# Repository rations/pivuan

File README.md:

<p align="center"><b>Devuan with sysvinit for the Raspberry Pi.</b></p>

---

Pivuan is a minimal [Devuan](https://www.devuan.org/) 6 "excalibur" image for the Raspberry Pi,
built with the [Armbian](https://www.armbian.com/) build framework. It boots with **sysvinit**
instead of systemd, feels like an Armbian minimal image (fast boot, first-boot setup wizard,
configuration tool), and gets its updates from Devuan and from its own apt repository.

- **Minimal**: a small console system (about 850 MB used) with networking, SSH and the
  `pivuan-config` tool. Add only what you need.
- **sysvinit, no systemd**: `init` is PID 1, with elogind, eudev and ifupdown. Packages that
  would pull in systemd are left out.
- **Desktop in one command**: XFCE or MATE with a LightDM login screen, installed from the
  Devuan archive (with XLibre from the Pivuan apt repository) by `pivuan-config`, SonicDE
  (from KDE Plasma, built by Pivuan), or
  **Pivuan Audio** for music production (JWM and JACK), which also runs Windows plugins.
- **Kept up to date**: Devuan's security updates through apt, and the Raspberry Pi kernel,
  firmware, board support and `pivuan-config` through the Pivuan apt repository.

Pivuan is built for the **Raspberry Pi 5** and uses the Raspberry Pi Foundation's kernel. The
same image is built for the other 64-bit boards it supports (Raspberry Pi 3 and 4), which are
less tested.

## Download

Get the latest image from **[Releases](https://github.com/rations/pivuan/releases)**: the
`Pivuan_<version>_Rpi4b_excalibur_current_<kernel>_minimal.img.xz` file and its `.sha` file.

Check the download (optional):

```sh
sha256sum -c Pivuan_*.img.xz.sha
```

## Install

Write the image to a microSD card (8 GB or larger). Any of these works:

- **balenaEtcher**: pick the `.img.xz` file and the card, then Flash.
- **Raspberry Pi Imager**: *Choose OS* → *Use custom* → the `.img.xz` file. Don't use its
  "OS customisation" settings; Pivuan's first-boot wizard does that.
- **Linux command line** (replace `/dev/sdX` with your card; check with `lsblk`, this erases it):

  ```sh
  xzcat Pivuan_*.img.xz | sudo dd of=/dev/sdX bs=4M conv=fsync status=progress
  ```

The image is `xz`-compressed, not a tar archive: use `xzcat`, `unxz` or `xz -d`, not `tar`.

## First boot

1. Put the card in the Pi, connect a screen and keyboard (or Ethernet), and power on.
2. The filesystem grows to fill the card and the **Pivuan setup wizard** starts on the screen.
   It asks for:
   - a new **root password**,
   - your **user name and password** (this user can use `sudo`, and always with a password;
     there is no automatic login),
   - Wi-Fi, if no network cable is plugged in.

   It also sets your time zone and language.
3. You end up at a shell with a welcome screen showing the system's state and tips.

Without a screen, connect Ethernet, find the Pi's address on your router and log in with
`ssh root@<address>` using the password **`1234`**; the same wizard then starts and makes you
change it.

## Boot splash

While Pivuan starts, the screen shows the Pivuan logo: a band of light sweeps it in, then
electricity runs along its circuit traces until the login appears. It also shows at shutdown
and restart. This is plymouth with the Pivuan theme (`pivuan-plymouth-theme`), which is on the
image and is installed with each desktop.

- Press **Esc** during the boot to see the boot messages instead.
- To turn the splash off, add `nosplash` to the line in `/boot/firmware/cmdline.txt` and
  restart. Remove it again to bring the splash back.

## Desktop

The image is minimal on purpose. To add a desktop, log in and install **Pivuan Audio**,
the desktop Pivuan is made for, or XFCE, MATE or SonicDE.

One desktop is installed at a time. To change to another one, remove the desktop first, from
the text login and not from a terminal in the desktop: removing it closes the desktop, and the
removal with it. Press **Ctrl+Alt+F1** for the text login (Pivuan Audio has its login screen on
tty1, so use **Ctrl+Alt+F2** there), log in and run the remove command of your desktop
(`AUDI02`, `XFCE02`, `MATE02` or `SONI02` in place of `01`).

### Pivuan Audio

A desktop for audio production on the Raspberry Pi 5, with JACK and PulseAudio and without
PipeWire:

```sh
sudo pivuan-config --cmd AUDI01    # Pivuan Audio
```

It installs:

- **JWM** on the **XLibre** X server, built for Devuan excalibur (no backports) and installed
  from the Pivuan apt repository, with the **picom** compositor for smooth window moves,
- the **xlogin** login screen on tty1 instead of a display manager (it appears as soon as the
  install finishes; tty2 to tty6 keep their text login),
- **JACK** with realtime scheduling for the `audio` group, and the Pivuan audio applications
  from the Pivuan apt repository: Jack Graph, JackDAW, NAMp, NAMix, lvtuner, DRUMix and
  CPU Power, and **TONE3000** (its amp and effects plug-in as VST3 and LV2, and the standalone
  program, for every user; tones download from tone3000.com),
- **vstbridge** for 64-bit and 32-bit Windows VST2, VST3 and CLAP plugins in the audio
  programs ("vstbridgectl" in the Audio menu), with **Wine** and **FEX** for Windows programs,
  such as plugin installers and license managers: they open from a right-click in pcmanfm
  ("Wine Windows Program Loader"). Installed Windows programs are in the **Wine** menu, which
  updates itself, with Wine Configuration and Uninstall Windows Programs, and the shortcuts
  installers put on the desktop show as desktop icons. Plugins protected by iLok (PACE),
  such as Neural DSP's, run with a license activated to the computer in iLok License Manager
  (USB iLok keys don't work in Wine). They, and iLok License Manager, need iLok's service
  running before they open: open **Plugin Licenses** in the Audio menu, wait for "Ready" (about
  half a minute), then open your DAW or iLok License Manager. Once the plugins have loaded you
  can close the window; the service (about 1 GB of memory) stops by itself when you close the
  DAW. A plugin that loads without it says it has
  no license; if JackDAW then skipped it, Options > Plugins… > Scan tries it again.
  Everything uses the Wine prefix `~/.wine`. How this works without DXVK:
  [wine-fex-info.md](wine-fex-info.md),
- **PulseAudio** for everything else: HDMI, Bluetooth speakers and headphones, the browser and
  media player. The speaker in the tray opens a volume slider with Mute and a button for
  Volume Control (pavucontrol); a right click opens Volume Control, and its scroll wheel
  changes the volume. A USB audio interface is an output as soon as it is plugged in (if
  PulseAudio leaves it at the profile Off, it is given its best output profile; if it could
  not open the interface, it is switched off and on again). While JACK
  runs, PulseAudio lets it have the sound card and plays into JACK instead ("JACK (audio
  interface)" in Volume Control); when JACK stops, it takes the card back,
- lxterminal, pcmanfm, mousepad, Celluloid, lxrandr and lxappearance, with the Pivuan icons
  (drawn for the Haiku operating system). In pcmanfm and on the desktop, a right click on a
  zip or tar archive (.zip, .tar, .tar.gz, .tar.xz, .tar.bz2, .tar.zst) has **Extract Here**:
  it unpacks next to the archive, into a folder named after it when it holds several files,
  and never overwrites anything.
  **Extra monitors**: Settings > Monitor Settings (lxrandr, "Display Settings") sets each
  monitor's resolution and where it is. The first monitor in its list stays put (its Position
  is greyed out); each other one is placed on its left or right ("On left", "On right"), above
  or below it, or shows the same picture: that is "Default" (best when both have the same
  resolution). After Apply, confirm within 15 seconds, or the old layout comes back. Save
  keeps it: the saved layout is applied at each login, as are other programs in
  `~/.config/autostart` meant for LXDE or any desktop. Every monitor gets its own desktop with
  the background, and with a touchscreen, touch stays on the touchscreen's own monitor (a
  Raspberry Pi touch display, or else the smallest monitor),
- the folders Desktop, Downloads, Documents, Music, Videos, NAM, Impulse Responses, `.vst3`
  and `.lv2` in each home, bookmarked in pcmanfm (the files in Desktop show on the desktop),
- **NetworkManager** and **blueman** in the tray, and **Brave Origin**,
- **Desktop Settings** (Settings in the menu), in four tabs that fit small screens:
  **Background** (the Pivuan backgrounds, black by default, or any picture, and icons on the
  desktop, on by default), **Screen** (the **brightness**, turning the screen off after 10
  minutes without use, off by default, and long press on a touchscreen), **Panel** (its size,
  color, by default the grey of the Pivuan logo, hiding it until the mouse reaches the bottom
  edge, and the on-screen keyboard) and **Panel Icons** (program icons on the panel, all drawn
  at the same size). **Apply** lights up when there is a change to apply. It saves to
  `~/.config/pivuan/desktop.conf`. Brightness uses the screen's backlight, or the monitor's
  own setting over HDMI (DDC/CI), or else dims the picture; the sun button on the panel opens
  just the brightness slider.

**Screenshots**: Print saves the whole screen, Alt+Print an area you drag out, and
Super+Print a window you click, as PNG files in `~/Pictures`. **Accessories > Screenshot** in
the menu takes the same three, after a delay if you like, then lets you name the picture and
choose its folder (`~/Pictures` at first).

The **Pivuan menu** (jgmenu) is on the Pivuan button in the tray, on a right click on the
desktop, and on Alt+F1. It has Terminal, Home and Web Browser, then the programs by category
(Accessories, Audio, Video, Internet, Settings, System and so on, from the programs' own menu
entries, so a program you install shows up in its category by itself), the Windows programs
installed in Wine, and Log Out, Reboot and Shut Down, which ask first. Its look is in
`/etc/pivuan/jgmenurc`; settings in `~/.config/jgmenu/jgmenurc` override it. Each user's
`~/.jwmrc` includes `/etc/jwm/pivuan.jwmrc`; add your own settings to
`~/.jwmrc`. `sudo pivuan-config --cmd AUDI02` removes it and brings back the text login.

#### Touchscreens

Pivuan Audio works on a touchscreen with no keyboard attached. When a touchscreen is
connected:

- The **login screen** shows an on-screen keyboard under the login box, in the keyboard
  layout chosen at first boot. **Keyboard** on the login screen, or **Hide** on the
  keyboard, puts it away and brings it back. Options → On-screen keyboard sets it to
  Automatic, Always or Never. With **Log in automatically** ticked, the machine starts
  without asking for a password at all.
- The **desktop** has a keyboard button on the panel that shows and hides **Onboard**, the
  on-screen keyboard, docked above the panel. It is also Settings → On-screen Keyboard in the
  menu. In Desktop Settings, set it to Automatic (only with a touchscreen), Always or Never.
- **Long press for right click:** hold a finger still for a moment and lift it, for the
  menus a right click opens (JackDAW's track and record menus, disconnecting in jack-graph,
  pcmanfm and the desktop). A tap is a click, and a moving finger drags: dials, selections,
  and window borders and corners to resize them. Pinch to zoom in the web browser is off
  while it runs; Desktop Settings → Screen turns it off.
- **Two fingers scroll:** move two fingers up and down (or sideways) and the page or list
  under them follows, wherever the mouse wheel scrolls (it turns the wheel).
- **Onboard comes up by itself** when you tap a text box in GTK and Qt programs and in the
  web browser, and goes away afterwards; the panel button is for the rest. It stays down
  while a USB or Bluetooth keyboard is plugged in.
- The panel is 48 pixels and its icons 32, window borders and title bars are bigger, and
  tooltips are off (a tap would leave them standing). Desktop Settings changes the panel.
- In GTK 3 programs (JackDAW, Desktop Settings, pcmanfm) a tap is a mouse click, so their
  drop-down lists stay open and dragging works; scroll their lists with two fingers or
  the scroll bars.
- If the screen is powered from the Pi's USB, an audio interface on the same USB can be too
  much for it: the Pi 5 gives USB 600 mA in all unless its supply is the 5 A one. Power the
  screen separately, or plug the interface in before starting.

A touchscreen is an input device the kernel marks as *direct*
(`/sys/class/input/input*/properties`). A touchpad or a mouse does not count.

### XFCE and MATE

General-purpose desktops:

```sh
sudo pivuan-config --cmd XFCE01    # XFCE
sudo pivuan-config --cmd MATE01    # MATE
```

This installs, from the Devuan archive:

- **XFCE** with `xfce4-terminal` and the Pivuan menu icon, or **MATE** with `mate-terminal`,
  both with the black Pivuan background,
- the **XLibre** X server from the Pivuan apt repository (as on Pivuan Audio), with the
  **picom** compositor for smooth window moves,
- the **LightDM** login screen (no automatic login),
- **NetworkManager** with its tray applet (your wired and Wi-Fi settings are moved over),
- **PulseAudio** for sound and Bluetooth audio,
- the **Pivuan icon theme** (the icons of the Haiku operating system), to pick in Appearance;
  the desktops keep the Numix icons,
- **Brave Origin** as the web browser, from [Brave's apt repository](https://brave.com/linux/).

When it finishes, the login screen appears. Log in with the user you created in the wizard.

### SonicDE

[SonicDE](https://github.com/Sonic-DE) is a desktop forked from KDE Plasma 6 that keeps to X11:

```sh
sudo pivuan-config --cmd SONI01    # SonicDE (about 1.5 GB)
```

SonicDE needs a newer Qt and KDE Frameworks than Devuan has, so Pivuan builds the whole desktop,
with its own Qt and frameworks, into `/opt/sonicde` and publishes it in an apt repository of its
own, the [Pivuan SonicDE apt repository](https://github.com/rations/pivuan-sonicde), which
`pivuan-config` adds (signed with the same key as the Pivuan apt repository). Devuan's own Qt
programs are left as they are. This installs:

- **SonicDE**: the desktop and panel, the sonic-win window manager (it draws its own effects,
  without picom), System Settings, the file manager, terminal, system monitor, screenshot tool
  and disk tool, with the **Silver Dark** look, the panel along the bottom and the
  SonicBallLightning background (the lock screen keeps the black Pivuan one),
- programs from Devuan that SonicDE has none of: **FeatherPad** (text editor), **VLC** (video
  and music), **LXQt Archiver**, **qpdfview** (PDF viewer), **LXImage** (image viewer) and
  **Qalculate** (calculator),
- the **XLibre** X server from the Pivuan apt repository, as on the other desktops,
- the **LightDM** login screen (no automatic login),
- **NetworkManager**, **PulseAudio** and **Bluetooth**, in the panel (your wired and Wi-Fi
  settings are moved over),
- **Onboard**, the on-screen keyboard, which comes up when a text box is tapped on a
  touchscreen,
- **Brave Origin** as the web browser, from [Brave's apt repository](https://brave.com/linux/).

When it finishes, the login screen appears. Log in with the user you created in the wizard.
`sudo pivuan-config --cmd SONI02` removes it, and the Pivuan SonicDE apt repository with it.

## pivuan-config

`pivuan-config` is the configuration tool: Armbian's `armbian-config` adapted for sysvinit.
Run it with a menu, or give it a command:

```sh
sudo pivuan-config                 # menu: system, network, localisation, software, desktops
sudo pivuan-config --cmd help      # list the commands
pivuan-config --help
pivuan-config --doc                # this README
```

Network settings: with a desktop installed, NetworkManager runs the network. Use the
network icon in the panel, or **Network → Network connections** in `pivuan-config` (the
same as `sudo nmtui`). On a console-only system, **Network → Switch to NetworkManager**
moves your wired and Wi-Fi settings over to it first.

## Updates

```sh
sudo apt update && sudo apt full-upgrade
```

- Everything from Devuan (the base system, the desktop, security fixes) comes from
  `deb.devuan.org`.
- The kernel, device trees, board support and `pivuan-config` come from the **Pivuan apt
  repository**, `https://rations.github.io/pivuan`, which Pivuan images already use. So do
  Pivuan Audio's XLibre, audio applications, vstbridge and Wine. The repository is
  signed with the key `34EA 4F11 5D83 793B 6C80  3155 4769 929F 204B 18CD`.

The kernel follows the Foundation's `rpi-6.18.y` long-term branch. Each week the build checks
for a new kernel point release (they carry the security fixes); when there is one, a new
image is released here and the kernel packages reach installed systems through `apt`.

## How Pivuan is made

Pivuan is a fork of the Armbian build framework that builds Devuan with sysvinit:

| Repository | What it is |
|---|---|
| [rations/build](https://github.com/rations/build) (branch `pivuan`) | Armbian build framework fork: Devuan excalibur support, sysvinit init scripts for Armbian's first-boot and board services, the image and apt-repository workflows |
| [rations/configng](https://github.com/rations/configng) | `armbian-config` (configng) fork, packaged as `pivuan-config`: a sysvinit service backend and the Devuan desktop install |
| [raspberrypi/linux](https://github.com/raspberrypi/linux) | The Raspberry Pi Foundation's kernel, pinned to a tested `rpi-6.18.y` commit |
| [rations/pivuan](https://github.com/rations/pivuan) (this repository) | Project page, releases (images), the apt repository (`gh-pages` branch), and the XLibre, vstbridge, Pivuan icon theme, boot splash, Desktop Settings and long press package builds |
| [rations/vstbridge](https://github.com/rations/vstbridge) (branch `arm64`) | vstbridge, the Windows plugin bridge, and the build of its Wine with FEX ([wine-fex-info.md](wine-fex-info.md)) |

Images are built by GitHub Actions in `rations/build`, from Devuan packages checked against
Devuan's signing keys. The packages in the image, in each desktop and in the Pivuan apt
repository are listed in [packages/](packages/).

## Thanks

Pivuan exists because of the work of two projects:

- **[Armbian](https://www.armbian.com/)**: the build framework, board support, first-boot
  wizard, `armbian-config` and the kernel packaging are theirs. Pivuan is their work, adapted
  to boot without systemd. Please support them: <https://www.armbian.com/donate/>
- **[Devuan](https://www.devuan.org/)**: the whole operating system, init freedom, and years
  of keeping Debian usable without systemd. Please support them: <https://www.devuan.org/os/donate>

Also thanks to the [Raspberry Pi Foundation](https://www.raspberrypi.com/) for the kernel and
firmware, to [Debian](https://www.debian.org/), which Devuan is based on, and to the
[Haiku](https://www.haiku-os.org/) project, whose icons make up the Pivuan icon theme.

Pivuan is an independent personal project. It is not affiliated with or endorsed by Armbian,
Devuan, Debian, Raspberry Pi Ltd or Haiku, Inc.

## License

The contents of this repository are licensed under the
[GNU General Public License, version 2](LICENSE), the license of the Armbian build framework
Pivuan is built with, **except the Pivuan artwork** and the Pivuan icon theme.

**Pivuan icon theme.** The icons in [icon-theme/](icon-theme/) were drawn by the artists of
the Haiku project and, with the scripts that build the theme, are under the MIT license (its
`LICENSE` and `CREDITS.md`). "HAIKU" and the HAIKU logo are trademarks of Haiku, Inc.

**Pivuan artwork.** The Pivuan logo and backgrounds (`pivuan-logo.png`, the animated
`pivuan-logo.gif` and `pivuan-splash.gif`, `backgrounds/background-*.png`, and the copies of
them in Pivuan images and in
[rations/configng](https://github.com/rations/configng)) are © 2026 rations, all rights
reserved. They are not covered by the GPL or any other license in these repositories, and may
only be used with permission. Please ask by
[opening an issue](https://github.com/rations/pivuan/issues).

The images contain software under many licenses (the Linux kernel is GPL-2.0; Devuan and
Debian packages keep their own licenses, listed in `/usr/share/doc/*/copyright` on the
system). Source code: the build framework in [rations/build](https://github.com/rations/build)
(GPL-2.0), `pivuan-config` in [rations/configng](https://github.com/rations/configng)
(GPL-3.0), the kernel in [raspberrypi/linux](https://github.com/raspberrypi/linux), vstbridge
(GPL-3.0) and the build of its Wine (LGPL-2.1-or-later) and FEX (MIT) in
[rations/vstbridge](https://github.com/rations/vstbridge), TONE3000 (MIT, built with the JUCE
framework under the AGPL-3.0) in
[tone-3000/tone3000-plugin](https://github.com/tone-3000/tone3000-plugin) at the release that
rations/build's `.github/pivuan/apps/apps.conf` names, and every Devuan package from Devuan's
source archive (`apt source <package>`).

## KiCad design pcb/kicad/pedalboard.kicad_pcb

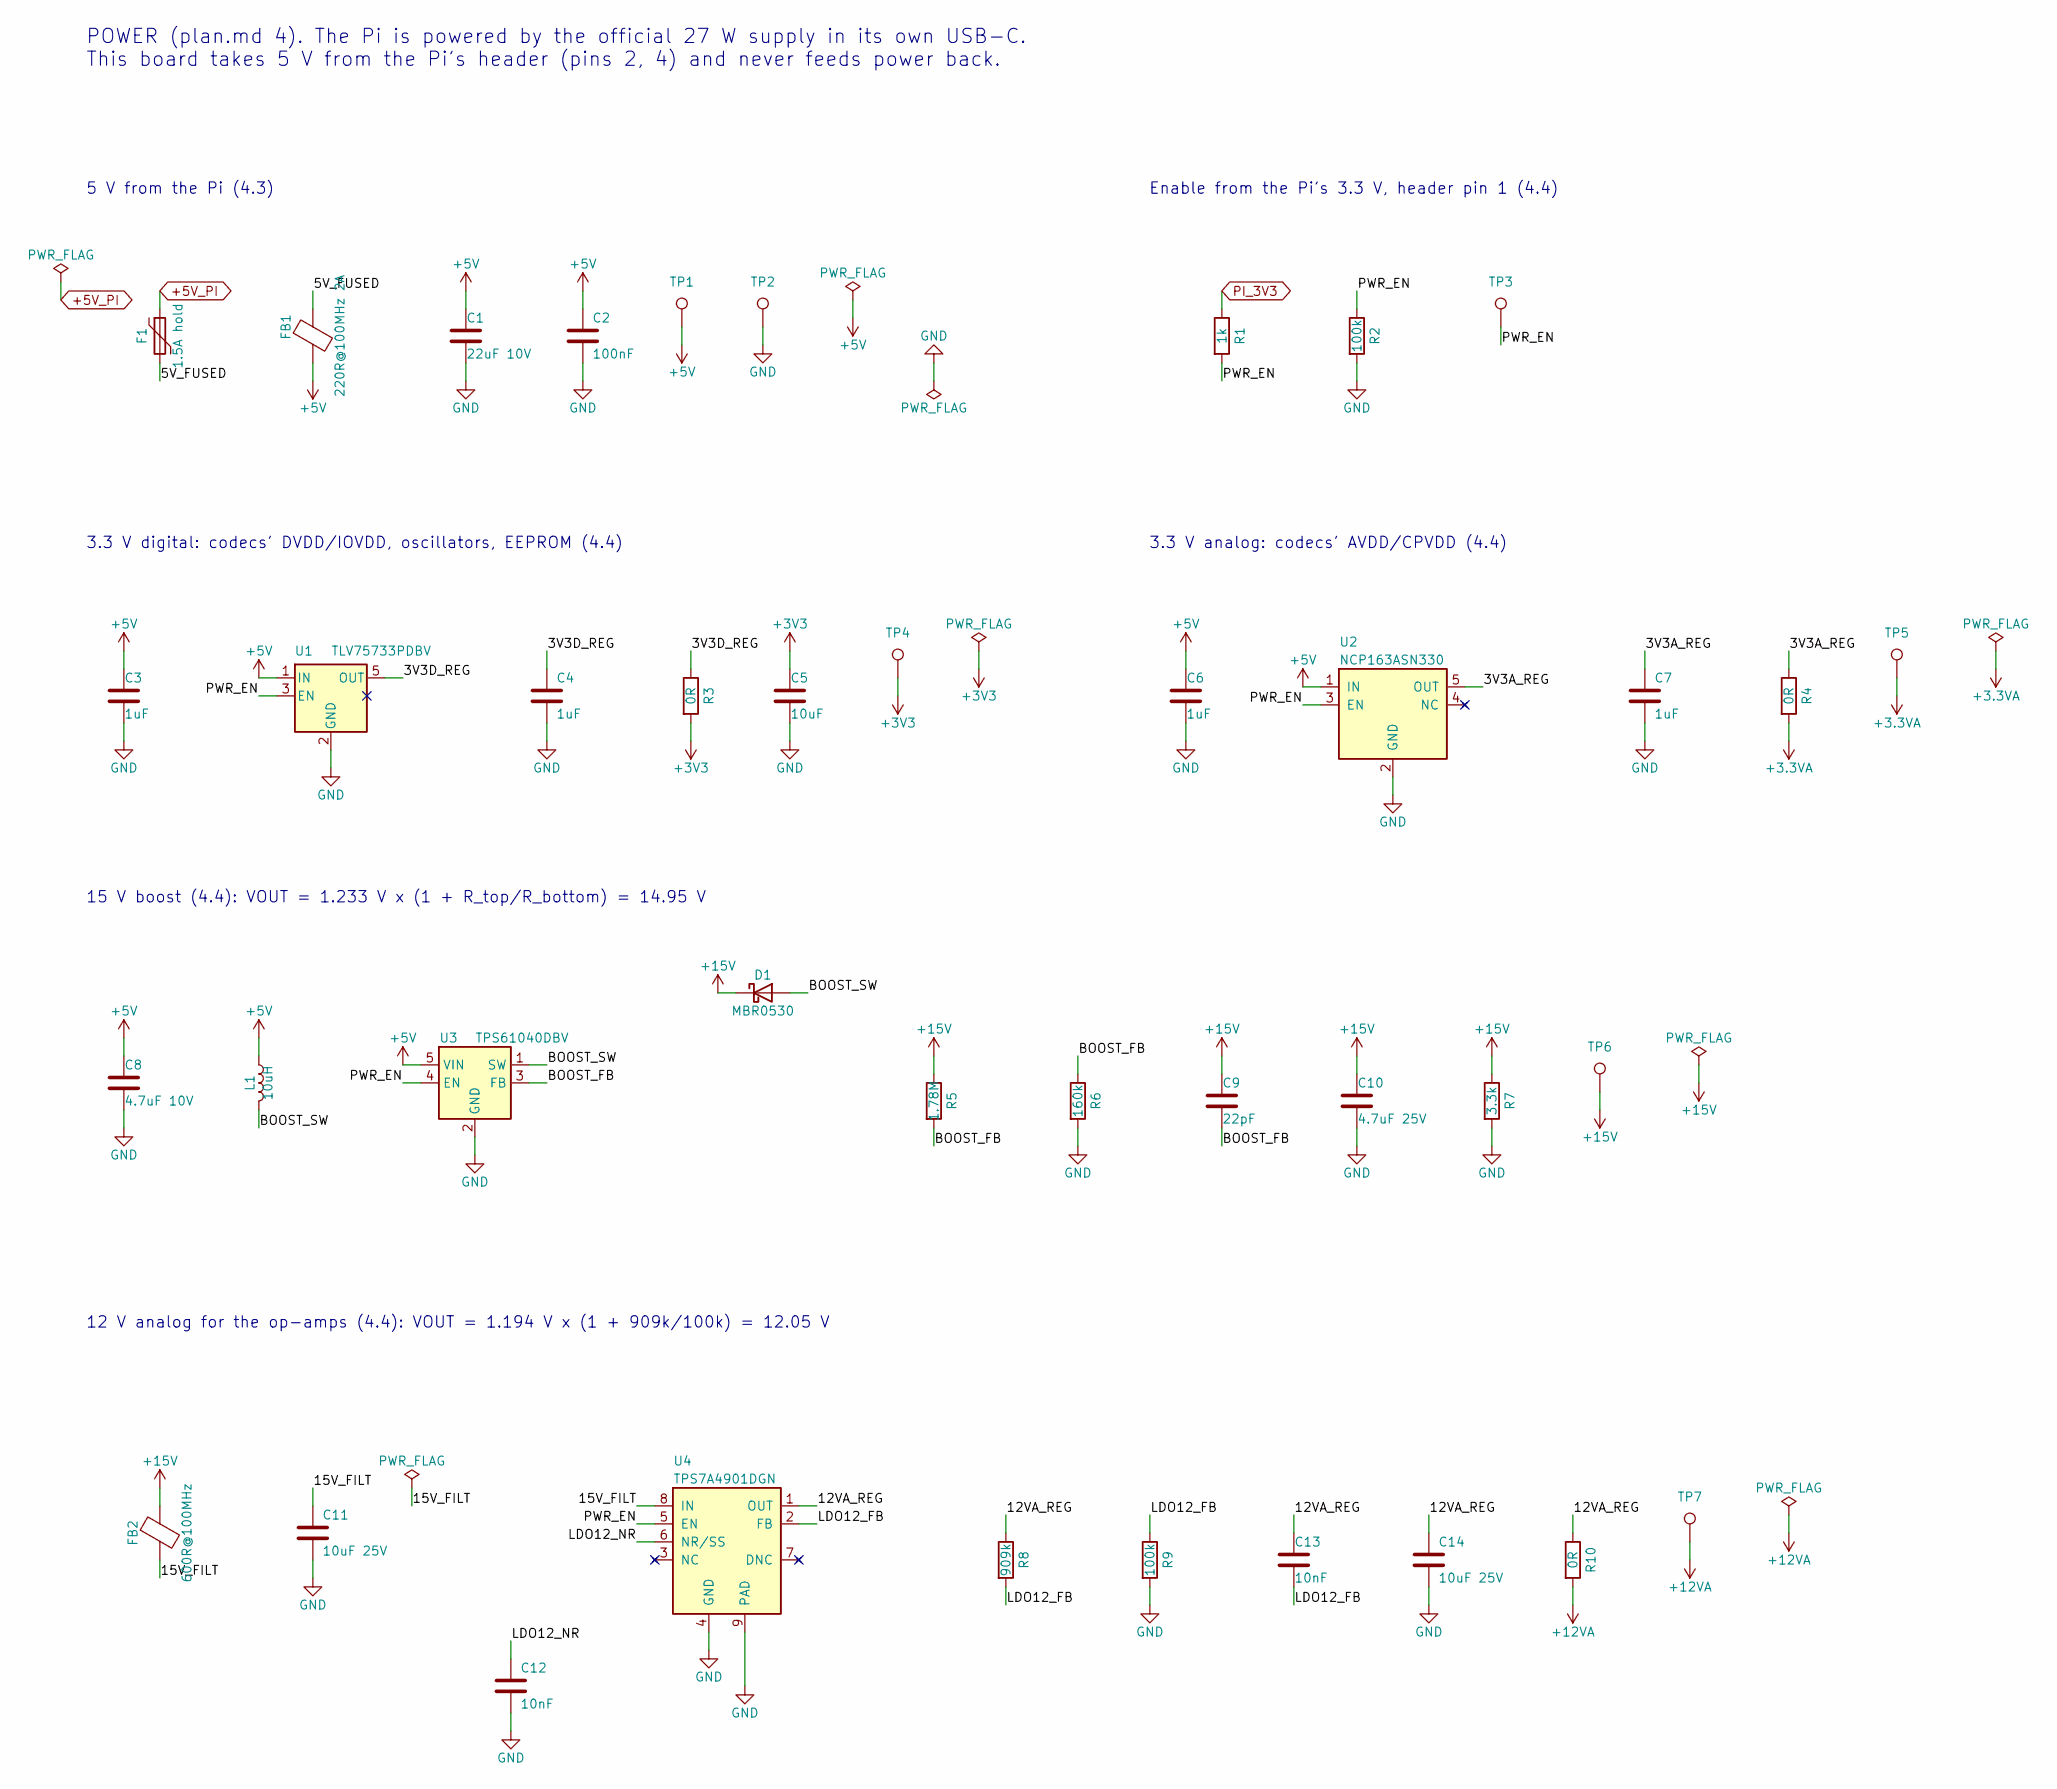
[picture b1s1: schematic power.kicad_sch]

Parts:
C1: 22uF 10V; C_1206_3216Metric; MPN CL31A226KAHNNNE; LCSC C12891
C2: 100nF; C_0603_1608Metric; MPN CC0603KRX7R9BB104; LCSC C14663
C3, C4, C6, C7: 1uF; C_0603_1608Metric; MPN CL10A105KB8NNNC; LCSC C15849
C5: 10uF; C_0805_2012Metric; MPN CL21A106KAYNNNE; LCSC C15850
C8: 4.7uF 10V; C_0805_2012Metric; MPN CL21A475KAQNNNE; LCSC C1779
C9: 22pF; C_0603_1608Metric; MPN CL10C220JB8NNNC; LCSC C1653
C10: 4.7uF 25V; C_1210_3225Metric; MPN CL32B475KBUYNNE; LCSC C170099
C11, C14: 10uF 25V; C_1206_3216Metric; MPN CL31A106KBHNNNE; LCSC C13585
C12, C13: 10nF; C_0603_1608Metric; MPN 0603B103K500NT; LCSC C57112
D1: MBR0530; D_SOD-123; MPN MBR0530T1G; LCSC C82046
F1: 1.5A hold; Fuse_1812_4532Metric; MPN MF-MSMF150-2; LCSC C89648
FB1: 220R@100MHz 2A; L_0805_2012Metric; MPN BLM21PG221SN1D; LCSC C85840
FB2: 600R@100MHz; L_0603_1608Metric; MPN BLM18KG601SN1D; LCSC C85833
L1: 10uH; L_1210_3225Metric; MPN LQH32PN100MN0L; LCSC C98020
R1: 1k; R_0603_1608Metric; MPN 0603WAF1001T5E; LCSC C21190
R2, R9: 100k; R_0603_1608Metric; MPN 0603WAF1003T5E; LCSC C25803
R3, R4, R10: 0R; R_0603_1608Metric; MPN 0603WAF0000T5E; LCSC C21189
R5: 1.78M; R_0603_1608Metric; MPN 0603WAF1784T5E; LCSC C59295
R6: 160k; R_0603_1608Metric; MPN 0603WAF1603T5E; LCSC C22813
R7: 3.3k; R_0805_2012Metric; MPN 0805W8F3301T5E; LCSC C26010
R8: 909k; R_0603_1608Metric; MPN AC0603FR-07909KL; LCSC C138276
TP1: +5V; TestPoint_Pad_D1.5mm
TP2: GND; TestPoint_Pad_D1.5mm
TP3: PWR_EN; TestPoint_Pad_D1.5mm
TP4: +3V3; TestPoint_Pad_D1.5mm
TP5: +3.3VA; TestPoint_Pad_D1.5mm
TP6: +15V; TestPoint_Pad_D1.5mm
TP7: +12VA; TestPoint_Pad_D1.5mm
U1: TLV75733PDBV; SOT-23-5; MPN TLV75733PDBVR; LCSC C485517
U2: NCP163ASN330; SOT-23-5; MPN NCP163ASN330T1G; LCSC C603656
U3: TPS61040DBV; SOT-23-5; MPN TPS61040DBVR; LCSC C7722
U4: TPS7A4901DGN; HVSSOP-8-1EP_3x3mm_P0.65mm_EP1.57x1.89mm; MPN TPS7A4901DGNR; LCSC C16430

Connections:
+3.3VA: R4.2, TP5.1; also elsewhere on the board
+3V3: C5.1, R3.2, TP4.1; also elsewhere on the board
+5V: C1.1, C2.1, C3.1, C6.1, C8.1, FB1.2, L1.1, TP1.1, U1.1 (IN), U2.1 (IN), U3.5 (VIN); also elsewhere on the board
+5V_PI: F1.1; also elsewhere on the board
+12VA: R10.2, TP7.1; also elsewhere on the board
+15V: C9.1, C10.1, D1.1 (K), FB2.1, R5.1, R7.1, TP6.1
/Power/3V3A_REG: C7.1, R4.1, U2.5 (OUT)
/Power/3V3D_REG: C4.1, R3.1, U1.5 (OUT)
/Power/5V_FUSED: F1.2, FB1.1
/Power/12VA_REG: C13.1, C14.1, R8.1, R10.1, U4.1 (OUT)
/Power/15V_FILT: C11.1, FB2.2, U4.8 (IN)
/Power/BOOST_FB: C9.2, R5.2, R6.1, U3.3 (FB)
/Power/BOOST_SW: D1.2 (A), L1.2, U3.1 (SW)
/Power/LDO12_FB: C13.2, R8.2, R9.1, U4.2 (FB)
/Power/LDO12_NR: C12.1, U4.6 (NR/SS)
/Power/PWR_EN: R1.2, R2.1, TP3.1, U1.3 (EN), U2.3 (EN), U3.4 (EN), U4.5 (EN)
GND: C1.2, C2.2, C3.2, C4.2, C5.2, C6.2, C7.2, C8.2, C10.2, C11.2, C12.2, C14.2, R2.2, R6.2, R7.2, R9.2, TP2.1, U1.2 (GND), U2.2 (GND), U3.2 (GND), U4.4 (GND), U4.9 (PAD); also elsewhere on the board
PI_3V3: R1.1; also elsewhere on the board

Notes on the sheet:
POWER (plan.md 4). The Pi is powered by the official 27 W supply in its own USB-C. This board takes 5 V from the Pi's header (pins 2, 4) and never feeds power back.
5 V from the Pi (4.3)
Enable from the Pi's 3.3 V, header pin 1 (4.4)
3.3 V digital: codecs' DVDD/IOVDD, oscillators, EEPROM (4.4)
3.3 V analog: codecs' AVDD/CPVDD (4.4)
15 V boost (4.4): VOUT = 1.233 V x (1 + R_top/R_bottom) = 14.95 V
12 V analog for the op-amps (4.4): VOUT = 1.194 V x (1 + 909k/100k) = 12.05 V

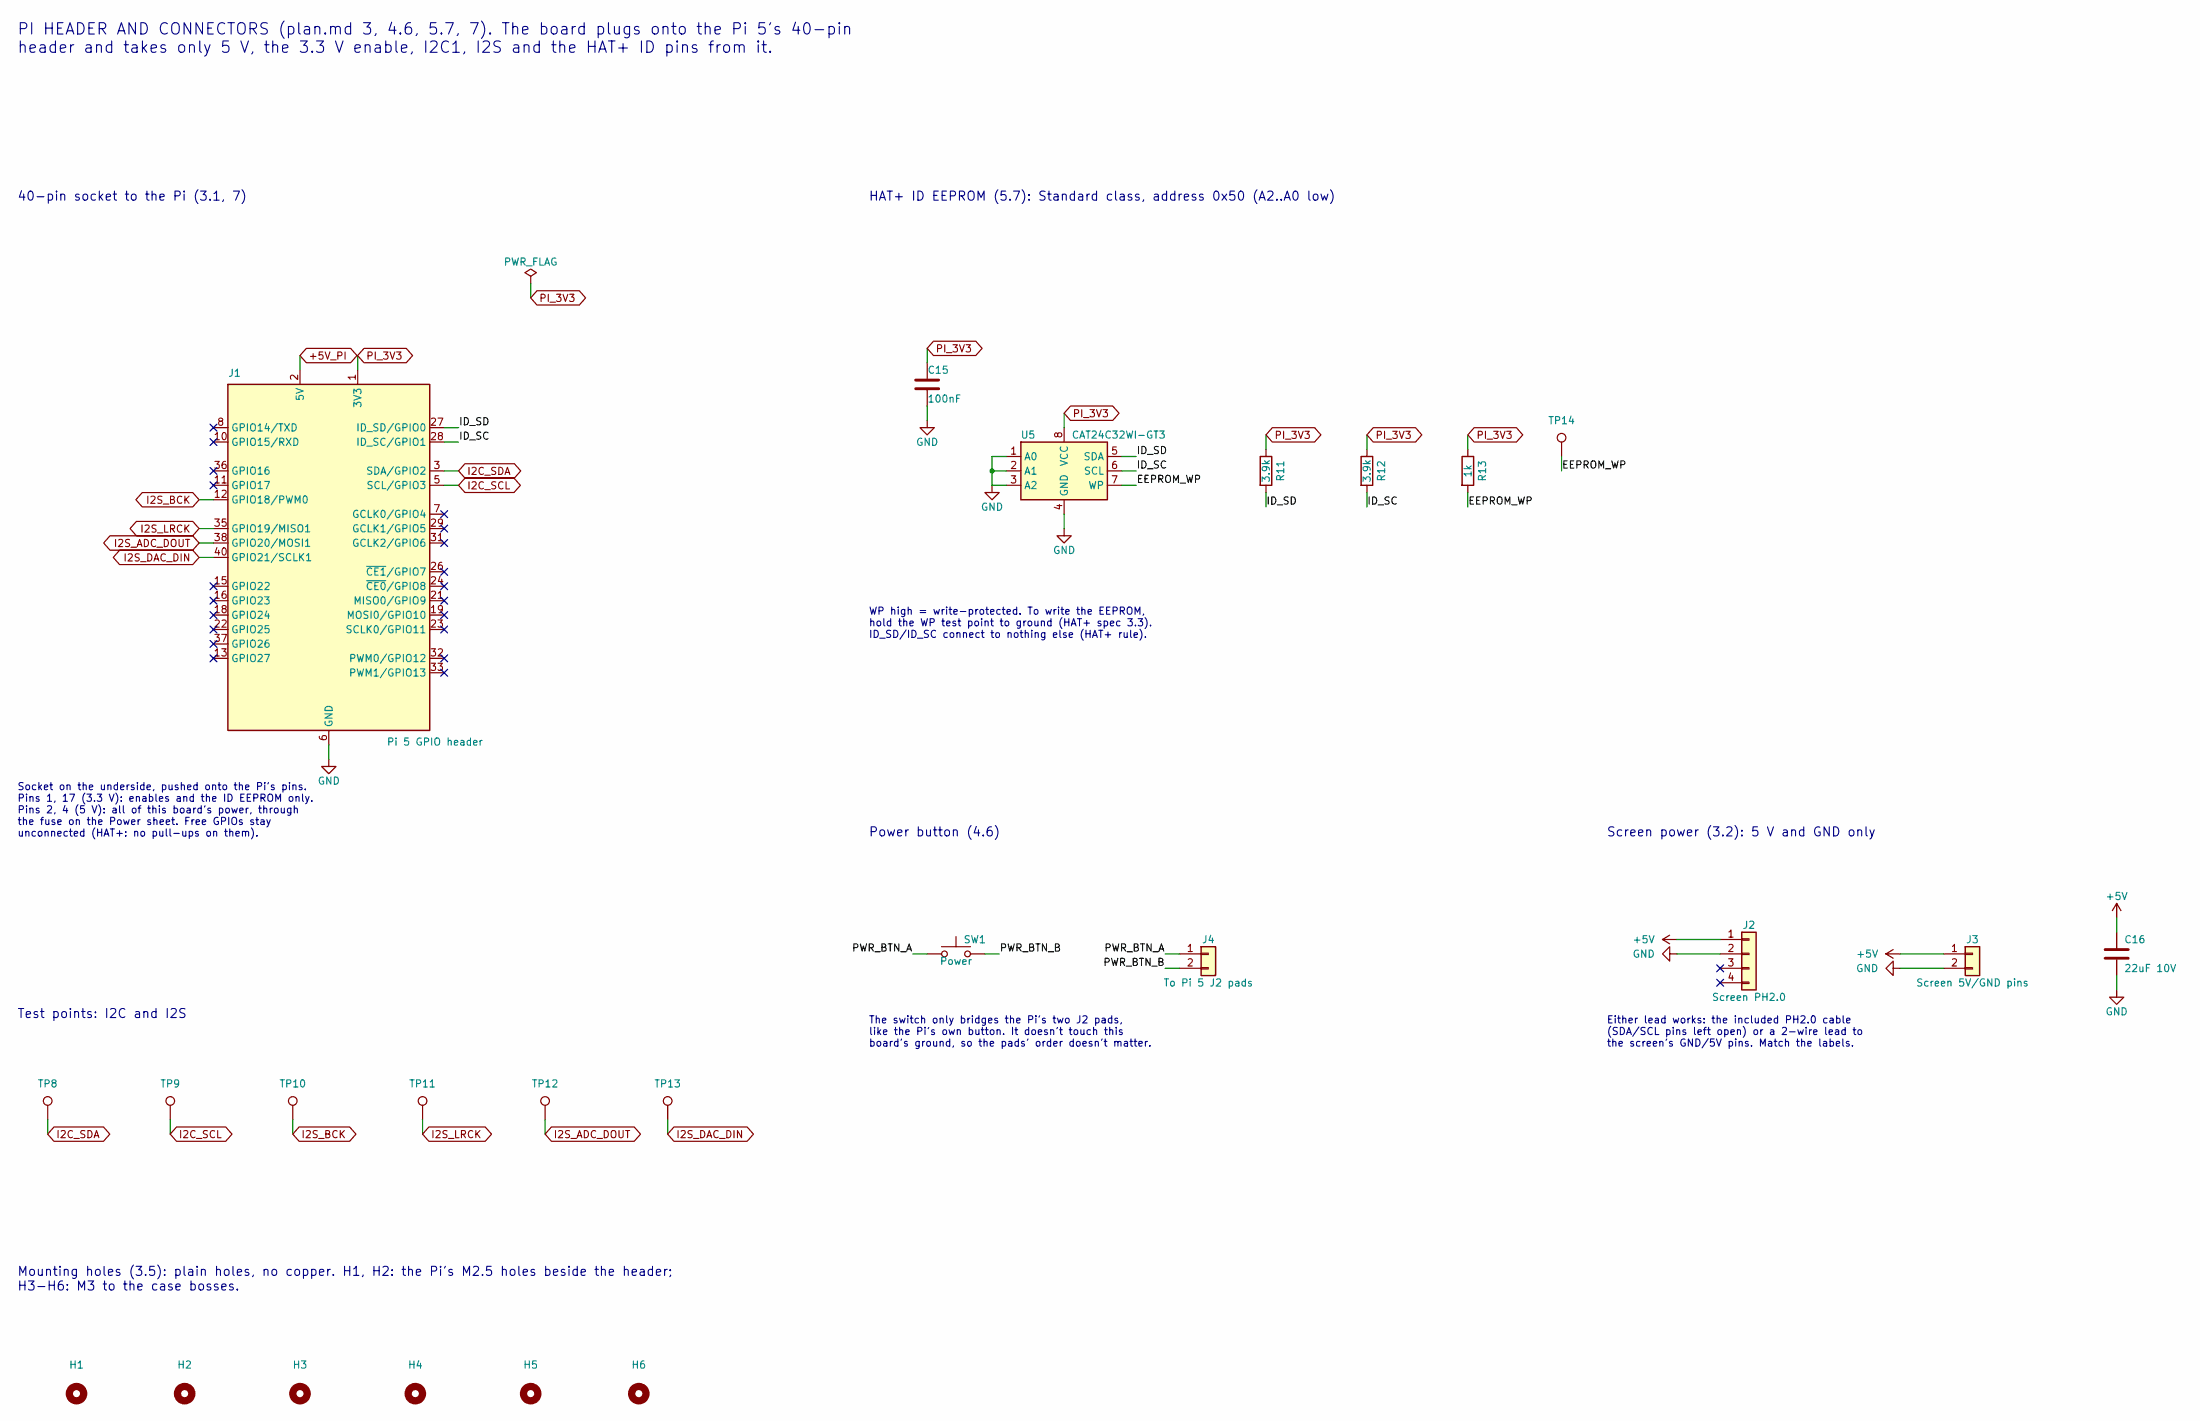
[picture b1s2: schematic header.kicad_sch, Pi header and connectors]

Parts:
C15: 100nF; C_0603_1608Metric; MPN CC0603KRX7R9BB104; LCSC C14663
C16: 22uF 10V; C_1206_3216Metric; MPN CL31A226KAHNNNE; LCSC C12891
H1, H2: Pi M2.5; MountingHole_2.7mm_M2.5
H3, H4, H5, H6: Case M3; MountingHole_3.2mm_M3
J1: Pi 5 GPIO header; PinSocket_2x20_P2.54mm_Vertical; MPN DS1023-2*20SF11; LCSC C132132
J2: Screen PH2.0; JST_PH_B4B-PH-K_1x04_P2.00mm_Vertical; MPN B4B-PH-K-S(LF)(SN); LCSC C131334
J3: Screen 5V/GND pins; PinHeader_1x02_P2.54mm_Vertical; MPN PZ254V-11-02P; LCSC C492401
J4: To Pi 5 J2 pads; JST_XH_B2B-XH-A_1x02_P2.50mm_Vertical; MPN B2B-XH-A(LF)(SN); LCSC C158012
R11, R12: 3.9k; R_0603_1608Metric; MPN 0603WAF3901T5E; LCSC C23018
R13: 1k; R_0603_1608Metric; MPN 0603WAF1001T5E; LCSC C21190
SW1: Power; SW_Tactile_SPST_Angled_PTS645Vx83-2LFS; MPN PTS645VL83-2 LFS
TP8: I2C_SDA; TestPoint_Pad_D1.5mm
TP9: I2C_SCL; TestPoint_Pad_D1.5mm
TP10: I2S_BCK; TestPoint_Pad_D1.5mm
TP11: I2S_LRCK; TestPoint_Pad_D1.5mm
TP12: I2S_ADC_DOUT; TestPoint_Pad_D1.5mm
TP13: I2S_DAC_DIN; TestPoint_Pad_D1.5mm
TP14: EEPROM_WP; TestPoint_Pad_D1.5mm
U5: CAT24C32WI-GT3; SOIC-8_3.9x4.9mm_P1.27mm; MPN CAT24C32WI-GT3; LCSC C81193

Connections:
+5V: C16.1, J2.1, J3.1; also elsewhere on the board
+5V_PI: J1.2 (5V), J1.4 (5V); also elsewhere on the board
/Pi header and connectors/EEPROM_WP: R13.2, TP14.1, U5.7 (WP)
/Pi header and connectors/ID_SC: J1.28 (ID_SC/GPIO1), R12.2, U5.6 (SCL)
/Pi header and connectors/ID_SD: J1.27 (ID_SD/GPIO0), R11.2, U5.5 (SDA)
/Pi header and connectors/PWR_BTN_A: J4.1, SW1.1
/Pi header and connectors/PWR_BTN_B: J4.2, SW1.2
GND: C15.2, C16.2, J1.6 (GND), J1.9 (GND), J1.14 (GND), J1.20 (GND), J1.25 (GND), J1.30 (GND), J1.34 (GND), J1.39 (GND), J2.2, J3.2, U5.1 (A0), U5.2 (A1), U5.3 (A2), U5.4 (GND); also elsewhere on the board
I2C_SCL: J1.5 (SCL/GPIO3), TP9.1; also elsewhere on the board
I2C_SDA: J1.3 (SDA/GPIO2), TP8.1; also elsewhere on the board
I2S_ADC_DOUT: J1.38 (GPIO20/MOSI1), TP12.1; also elsewhere on the board
I2S_BCK: J1.12 (GPIO18/PWM0), TP10.1; also elsewhere on the board
I2S_DAC_DIN: J1.40 (GPIO21/SCLK1), TP13.1; also elsewhere on the board
I2S_LRCK: J1.35 (GPIO19/MISO1), TP11.1; also elsewhere on the board
PI_3V3: C15.1, J1.1 (3V3), J1.17 (3V3), R11.1, R12.1, R13.1, U5.8 (VCC); also elsewhere on the board

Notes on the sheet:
PI HEADER AND CONNECTORS (plan.md 3, 4.6, 5.7, 7). The board plugs onto the Pi 5's 40-pin header and takes only 5 V, the 3.3 V enable, I2C1, I2S and the HAT+ ID pins from it.
40-pin socket to the Pi (3.1, 7)
Socket on the underside, pushed onto the Pi's pins. Pins 1, 17 (3.3 V): enables and the ID EEPROM only. Pins 2, 4 (5 V): all of this board's power, through the fuse on the Power sheet. Free GPIOs stay unconnected (HAT+: no pull-ups on them).
Test points: I2C and I2S
HAT+ ID EEPROM (5.7): Standard class, address 0x50 (A2..A0 low)
WP high = write-protected. To write the EEPROM, hold the WP test point to ground (HAT+ spec 3.3). ID_SD/ID_SC connect to nothing else (HAT+ rule).
Screen power (3.2): 5 V and GND only
Either lead works: the included PH2.0 cable (SDA/SCL pins left open) or a 2-wire lead to the screen's GND/5V pins. Match the labels.
Power button (4.6)
The switch only bridges the Pi's two J2 pads, like the Pi's own button. It doesn't touch this board's ground, so the pads' order doesn't matter.
Mounting holes (3.5): plain holes, no copper. H1, H2: the Pi's M2.5 holes beside the header; H3-H6: M3 to the case bosses.

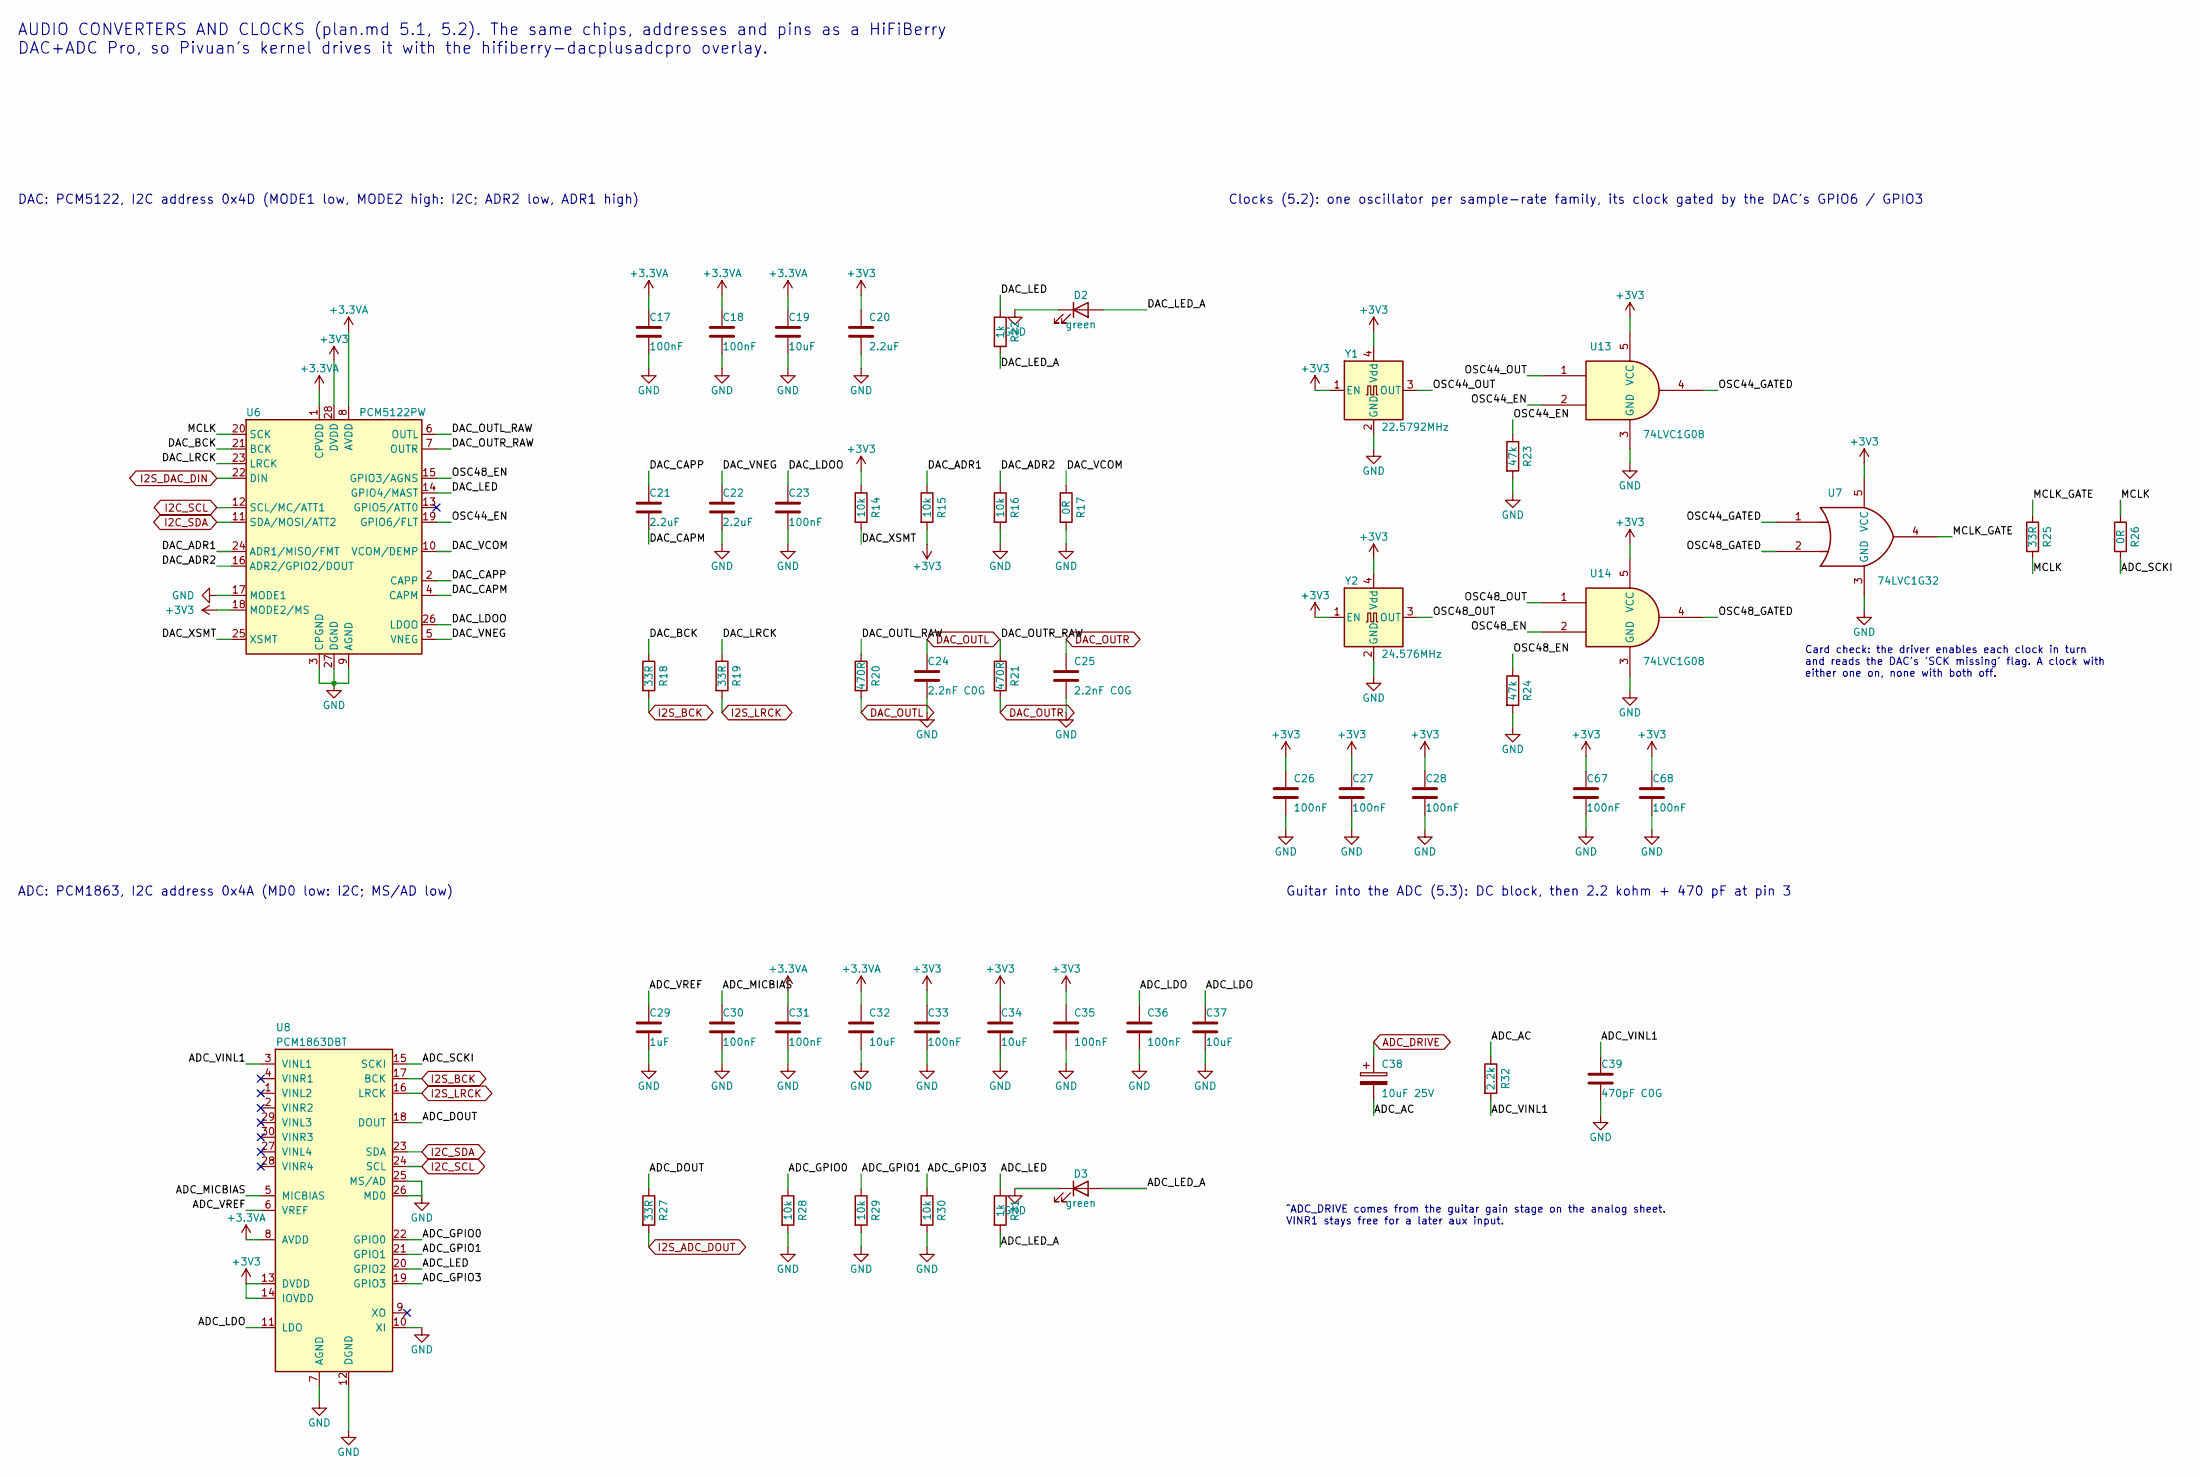
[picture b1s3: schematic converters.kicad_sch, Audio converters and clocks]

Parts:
C17, C18, C23, C26, C27, C28, C30, C31, C33, C35, C36, C67, C68: 100nF; C_0603_1608Metric; MPN CC0603KRX7R9BB104; LCSC C14663
C19, C32, C34, C37: 10uF; C_0805_2012Metric; MPN CL21A106KAYNNNE; LCSC C15850
C20, C21, C22: 2.2uF; C_0603_1608Metric; MPN CL10A225KO8NNNC; LCSC C23630
C24, C25: 2.2nF C0G; C_0603_1608Metric; MPN CC0603JRNPO9BN222; LCSC C107043
C29: 1uF; C_0603_1608Metric; MPN CL10A105KB8NNNC; LCSC C15849
C38: 10uF 25V; CP_Elec_5x5.4; MPN RVT1V100M0505; LCSC C72486
C39: 470pF C0G; C_0603_1608Metric; MPN GRM1885C1H471JA01D; LCSC C85979
D2, D3: green; LED_0603_1608Metric; MPN LTST-C191GKT; LCSC C99289
R14, R15, R16, R28, R29, R30: 10k; R_0603_1608Metric; MPN 0603WAF1002T5E; LCSC C25804
R17, R26: 0R; R_0603_1608Metric; MPN 0603WAF0000T5E; LCSC C21189
R18, R19, R25, R27: 33R; R_0603_1608Metric; MPN 0603WAF330JT5E; LCSC C23140
R20, R21: 470R; R_0603_1608Metric; MPN 0603WAF4700T5E; LCSC C23179
R22, R31: 1k; R_0603_1608Metric; MPN 0603WAF1001T5E; LCSC C21190
R23, R24: 47k; R_0603_1608Metric; MPN 0603WAF4702T5E; LCSC C25819
R32: 2.2k; R_0603_1608Metric; MPN 0603WAF2201T5E; LCSC C4190
U6: PCM5122PW; TSSOP-28_4.4x9.7mm_P0.65mm; MPN PCM5122PWR; LCSC C962071
U7: 74LVC1G32; SOT-23-5; MPN SN74LVC1G32DBVR; LCSC C10096
U8: PCM1863DBT; TSSOP-30_4.4x7.8mm_P0.5mm; MPN PCM1863DBTR; LCSC C529569
U13, U14: 74LVC1G08; SOT-23-5; MPN SN74LVC1G08DBVR; LCSC C7666
Y1: 22.5792MHz; Oscillator_SMD_Abracon_ASE-4Pin_3.2x2.5mm; MPN SX3M22.5792B10F20TNN; LCSC C7431341
Y2: 24.576MHz; Oscillator_SMD_Abracon_ASE-4Pin_3.2x2.5mm; MPN SX3M24.576B10F20TNN; LCSC C7431342

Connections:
+3.3VA: C17.1, C18.1, C19.1, C31.1, C32.1, U6.1 (CPVDD), U6.8 (AVDD), U8.8 (AVDD); also elsewhere on the board
+3V3: C20.1, C26.1, C27.1, C28.1, C33.1, C34.1, C35.1, C67.1, C68.1, R14.1, R15.2, U6.18 (MODE2/MS), U6.28 (DVDD), U7.5 (VCC), U8.13 (DVDD), U8.14 (IOVDD), U13.5 (VCC), U14.5 (VCC), Y1.1 (EN), Y1.4 (Vdd), Y2.1 (EN), Y2.4 (Vdd); also elsewhere on the board
/Audio converters and clocks/ADC_AC: C38.2, R32.1
/Audio converters and clocks/ADC_DOUT: R27.1, U8.18 (DOUT)
/Audio converters and clocks/ADC_GPIO0: R28.1, U8.22 (GPIO0)
/Audio converters and clocks/ADC_GPIO1: R29.1, U8.21 (GPIO1)
/Audio converters and clocks/ADC_GPIO3: R30.1, U8.19 (GPIO3)
/Audio converters and clocks/ADC_LDO: C36.1, C37.1, U8.11 (LDO)
/Audio converters and clocks/ADC_LED: R31.1, U8.20 (GPIO2)
/Audio converters and clocks/ADC_LED_A: D3.2 (A), R31.2
/Audio converters and clocks/ADC_MICBIAS: C30.1, U8.5 (MICBIAS)
/Audio converters and clocks/ADC_SCKI: R26.2, U8.15 (SCKI)
/Audio converters and clocks/ADC_VINL1: C39.1, R32.2, U8.3 (VINL1)
/Audio converters and clocks/ADC_VREF: C29.1, U8.6 (VREF)
/Audio converters and clocks/DAC_ADR1: R15.1, U6.24 (ADR1/MISO/FMT)
/Audio converters and clocks/DAC_ADR2: R16.1, U6.16 (ADR2/GPIO2/DOUT)
/Audio converters and clocks/DAC_BCK: R18.1, U6.21 (BCK)
/Audio converters and clocks/DAC_CAPM: C21.2, U6.4 (CAPM)
/Audio converters and clocks/DAC_CAPP: C21.1, U6.2 (CAPP)
/Audio converters and clocks/DAC_LDOO: C23.1, U6.26 (LDOO)
/Audio converters and clocks/DAC_LED: R22.1, U6.14 (GPIO4/MAST)
/Audio converters and clocks/DAC_LED_A: D2.2 (A), R22.2
/Audio converters and clocks/DAC_LRCK: R19.1, U6.23 (LRCK)
/Audio converters and clocks/DAC_OUTL_RAW: R20.1, U6.6 (OUTL)
/Audio converters and clocks/DAC_OUTR_RAW: R21.1, U6.7 (OUTR)
/Audio converters and clocks/DAC_VCOM: R17.1, U6.10 (VCOM/DEMP)
/Audio converters and clocks/DAC_VNEG: C22.1, U6.5 (VNEG)
/Audio converters and clocks/DAC_XSMT: R14.2, U6.25 (XSMT)
/Audio converters and clocks/MCLK: R25.2, R26.1, U6.20 (SCK)
/Audio converters and clocks/MCLK_GATE: R25.1, U7.4
/Audio converters and clocks/OSC44_EN: R23.1, U6.19 (GPIO6/FLT), U13.2
/Audio converters and clocks/OSC44_GATED: U7.1, U13.4
/Audio converters and clocks/OSC44_OUT: U13.1, Y1.3 (OUT)
/Audio converters and clocks/OSC48_EN: R24.1, U6.15 (GPIO3/AGNS), U14.2
/Audio converters and clocks/OSC48_GATED: U7.2, U14.4
/Audio converters and clocks/OSC48_OUT: U14.1, Y2.3 (OUT)
ADC_DRIVE: C38.1; also elsewhere on the board
DAC_OUTL: C24.1, R20.2; also elsewhere on the board
DAC_OUTR: C25.1, R21.2; also elsewhere on the board
GND: C17.2, C18.2, C19.2, C20.2, C22.2, C23.2, C24.2, C25.2, C26.2, C27.2, C28.2, C29.2, C30.2, C31.2, C32.2, C33.2, C34.2, C35.2, C36.2, C37.2, C39.2, C67.2, C68.2, D2.1 (K), D3.1 (K), R16.2, R17.2, R23.2, R24.2, R28.2, R29.2, R30.2, U6.3 (CPGND), U6.9 (AGND), U6.17 (MODE1), U6.27 (DGND), U7.3 (GND), U8.7 (AGND), U8.10 (XI), U8.12 (DGND), U8.25 (MS/AD), U8.26 (MD0), U13.3 (GND), U14.3 (GND), Y1.2 (GND), Y2.2 (GND); also elsewhere on the board
I2C_SCL: U6.12 (SCL/MC/ATT1), U8.24 (SCL); also elsewhere on the board
I2C_SDA: U6.11 (SDA/MOSI/ATT2), U8.23 (SDA); also elsewhere on the board
I2S_ADC_DOUT: R27.2; also elsewhere on the board
I2S_BCK: R18.2, U8.17 (BCK); also elsewhere on the board
I2S_DAC_DIN: U6.22 (DIN); also elsewhere on the board
I2S_LRCK: R19.2, U8.16 (LRCK); also elsewhere on the board

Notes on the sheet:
AUDIO CONVERTERS AND CLOCKS (plan.md 5.1, 5.2). The same chips, addresses and pins as a HiFiBerry DAC+ADC Pro, so Pivuan's kernel drives it with the hifiberry-dacplusadcpro overlay.
DAC: PCM5122, I2C address 0x4D (MODE1 low, MODE2 high: I2C; ADR2 low, ADR1 high)
Clocks (5.2): one oscillator per sample-rate family, its clock gated by the DAC's GPIO6 / GPIO3
Card check: the driver enables each clock in turn and reads the DAC's 'SCK missing' flag. A clock with either one on, none with both off.
ADC: PCM1863, I2C address 0x4A (MD0 low: I2C; MS/AD low)
Guitar into the ADC (5.3): DC block, then 2.2 kohm + 470 pF at pin 3
^ADC_DRIVE comes from the guitar gain stage on the analog sheet. VINR1 stays free for a later aux input.

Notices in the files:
pcb/kicad/converters.kicad_sch:
CERN-OHL-S-2.0
